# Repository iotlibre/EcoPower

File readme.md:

# EcoPower

Ecopower está pensado para tomar las medidas de consumo eléctrico de una vivienda o de un edificio con consumos inferiores a 30 KW. El sistema permite diferenciar varias zonas.

EcoPower se puede instalar en el cuadro eléctrico principal o en cualquier otra parte que nos permita tomar datos del consumo mediante pinzas (transformadores de intensidad).

En el un edificio podemos tener tantos dispositivos como sean necesarios y el servidor los integrará en la misma instalación sin necesidad de configuraciones adicionales o cambios en el Firmware.

La comunicación se hace mediante Wifi por lo que no es necesario el cableado de datos al equipo solamente es preciso que esté dentro de la cobertura de la red WIFI del edificio.

Para su uso no son necesarios conocimientos de informática aunque todos los desarrollos y el hardware están hechos bajo licencias libres lo que permite la modificación y mejora de las funcionalidades.

## Listado con las principales características
Las principales características de EcoPower son:
- 6 entradas para sensores de corriente con salida estandar de 50 mA
- 1 entrada de medida de voltage 200 - 440 Voltios
- Precisión en las medida de energía: ± 1,2%
- Comunicación a Internet por WIFI local 
- Configurable vía Web
- Estandard: IEEE 802.11 b/g/n
- Alimentación a 220 voltios de corriente alterna. Rango: 85 ~ 264VAC 
- Montaje en carril din
- La PCB integra un Arduino nano con el ESP8266 12E
- Compatible con el [servidor de Open Energy Monitor](https://emoncms.org/)

## Puesta a punto
La puesta a punto de EcoPower consta de dos partes:
- La configuración en la instalación
- El firmware de Arduino

### La configuración en la instalación
En este punto se definen los parámetros del servidor de destino y la wifi local a la que va a estar conectado el dispositivo. Con este fin, la primera vez que se ponga en servicio el ESP y siempre que no encuentre la WIFI configurada, el ESP 8266 12E creará su propio punto de acceso, su propia red WIFI . Conectandose a cualquier dirección a través de este punto de acceso nos aparecerá la página de configuración del ESP. Tengase en cuenta que una  vez configurado el ESP y conectado a una red WIFI el router le asignará una única dirección IP a la que será necesario acceder para cambiar la configuración.

En caso de que se quiera actualizar el firmware del ESP a la última versión, este se puede encontrar en: [EcoPower-emonESP ](https://github.com/iotlibre/20180328_EmonESP)

### El firmware de Arduino
El firmware que que esta cargado por defecto en el arduino nano funciona correctamente para tranformadores de intensidad de 100A/50mA sin embargo, si quiere cambiar la configuración puede encontrar la última actualización del firmware en este repositorio:[EcoPower-iotpow_serial ](https://github.com/iotlibre/EcoPower/tree/master/firmware/iotpower_serial/iotpow_serial)

## Source code
Copyright 2020 Endef Engineering SL.

Tanto el hardware como el software de este repositorio han sido desarrollados por la empresa: [Endef Engineering Sl](https://endef.com)

## Licencia
* Los diseños de hardware estan disponibles bajo licencia "Creative Commons Attribution-ShareAlike 3.0 Unported License.".
* El firmware se publica bajo la licencia GNU GPL V3 La documentación está sujeta a la Licencia "GNU Free Documentation"
* Los diseños de hardware siguen los términos de la Declaración de principios 1.0 de OSHW (Open-source hardware).

## Disclaimer
Todo el código que se encuentra en este repositorio está bajo la licencia: "GNU V3 General Public License" por lo que las condiciones de su uso son las incluidas en esta licencia

NUESTROS PRODUCTOS Y JUEGOS DE MONTAJE PUEDEN SER UTILIZADOS POR USUARIOS EXPERIMENTADOS Y CAPACITADOS BAJO SU PROPIO RIESGO. EN LA MEDIDA MÁXIMA QUE LO PERMITA LA LEY APLICABLE, POR EL PRESENTE RENUNCIAMOS CUALQUIER RESPONSABILIDAD, RIESGO Y DAÑOS DERIVADOS DE LA MUERTE O LESIONES PERSONALES RESULTANTES DEL MONTAJE O FUNCIONAMIENTO DE NUESTROS PRODUCTOS.

Su seguridad es su propia responsabilidad, incluido el uso adecuado del equipo y el equipo de seguridad, y determinar si tiene la habilidad y la experiencia adecuadas. Endef Engineering se exime de toda responsabilidad por cualquier daño, lesión o gasto resultante. Es su responsabilidad asegurarse de que sus actividades cumplan con las leyes aplicables, incluidos los derechos de autor. Puede haber actualizaciones o correcciones importantes. Todo uso de las instrucciones, kits, proyectos y sugerencias dadas por Endef Ingeniería es bajo su propio riesgo. La tecnología (hardware, firmware y software) cambia constantemente, es posible que la documentación (incluidas las instrucciones y la guía de compilación) no esté completa o sea correcta.

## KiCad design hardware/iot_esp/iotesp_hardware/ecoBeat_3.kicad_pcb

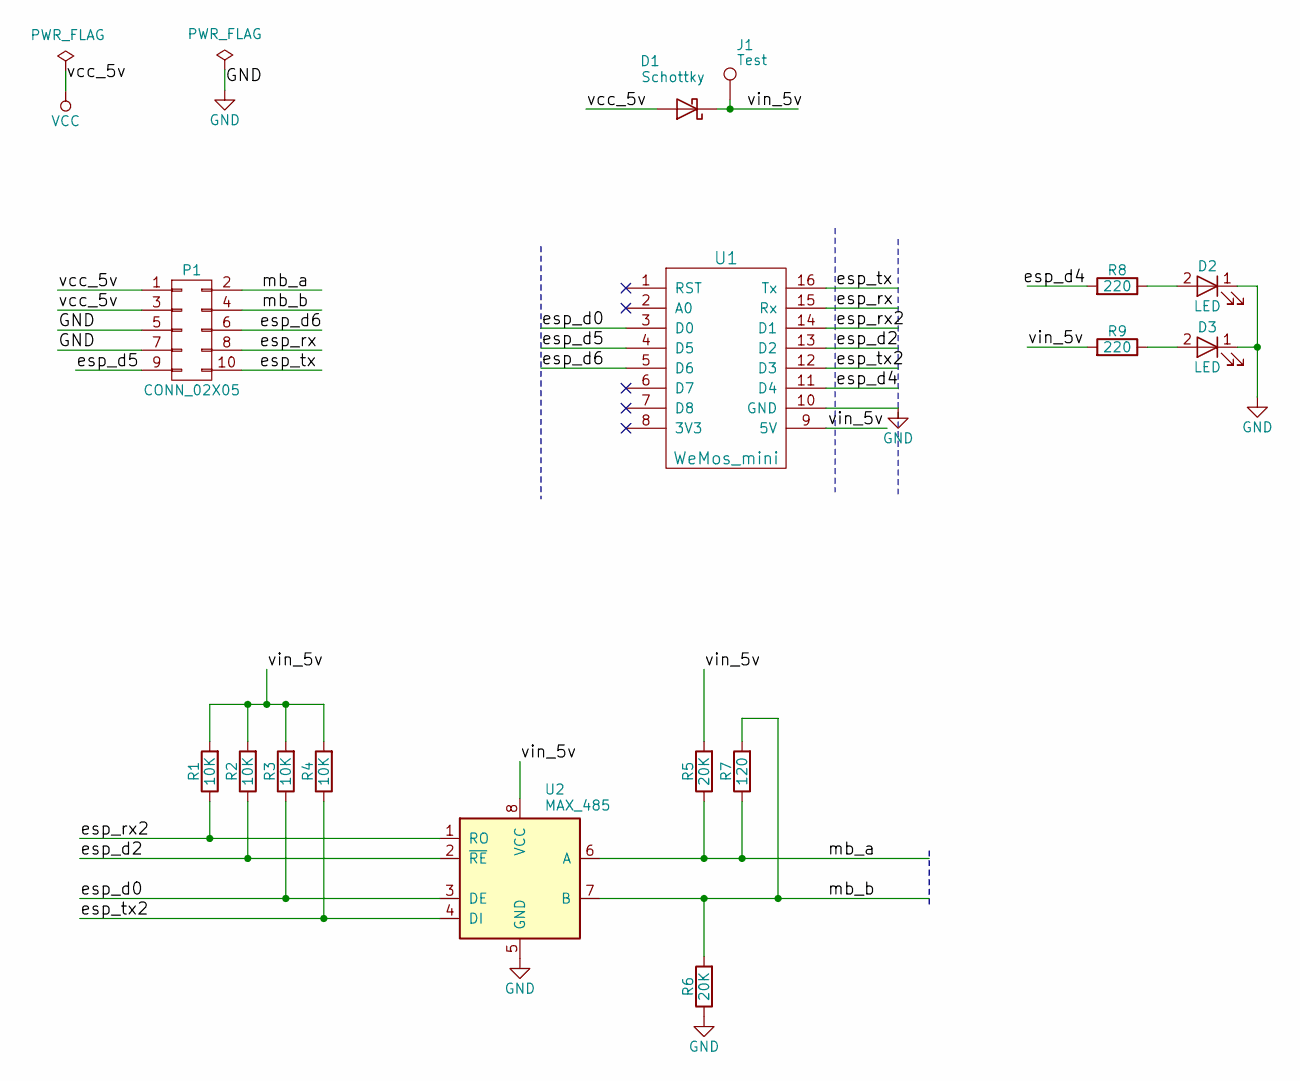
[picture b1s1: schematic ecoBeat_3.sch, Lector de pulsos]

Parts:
D1: Schottky; D_2114
D2, D3: LED; LED_D3.0mm
J1: Test; SolderWirePad_single_0-8mmDrill
P1: CONN_02X05; D1_mini_board
R1, R2, R3, R4: 10K; R_1206_HandSoldering
R5, R6: 20K; R_1206_HandSoldering
R7: 120; R_1206_HandSoldering
R8, R9: 220; R_1206_HandSoldering
U1: WeMos_mini; D1_mini_board_oscar
U2: MAX_485; SOIC-8-N

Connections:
/esp_d0: R3.1, U1.3 (D0), U2.3 (DE)
/esp_d2: R2.1, U1.13 (D2), U2.2 (~RE~)
/esp_d4: R8.2, U1.11 (D4)
/esp_d5: P1.9, U1.4 (D5)
/esp_d6: P1.6, U1.5 (D6)
/esp_rx: P1.8, U1.15 (Rx)
/esp_rx2: R1.1, U1.14 (D1), U2.1 (RO)
/esp_tx: P1.10, U1.16 (Tx)
/esp_tx2: R4.1, U1.12 (D3), U2.4 (DI)
/mb_a: P1.2, R5.1, R7.1, U2.6 (A)
/mb_b: P1.4, R6.2, R7.2, U2.7 (B)
/vin_5v: D1.1 (K), J1.1, R1.2, R2.2, R3.2, R4.2, R5.2, R9.2, U1.9 (5V), U2.8 (VCC)
GND: D2.1 (K), D3.1 (K), P1.5, P1.7, R6.1, U1.10 (GND), U2.5 (GND)
unnamed: D2.2 (A), R8.1
unnamed: D3.2 (A), R9.1
VCC: D1.2 (A), P1.1, P1.3

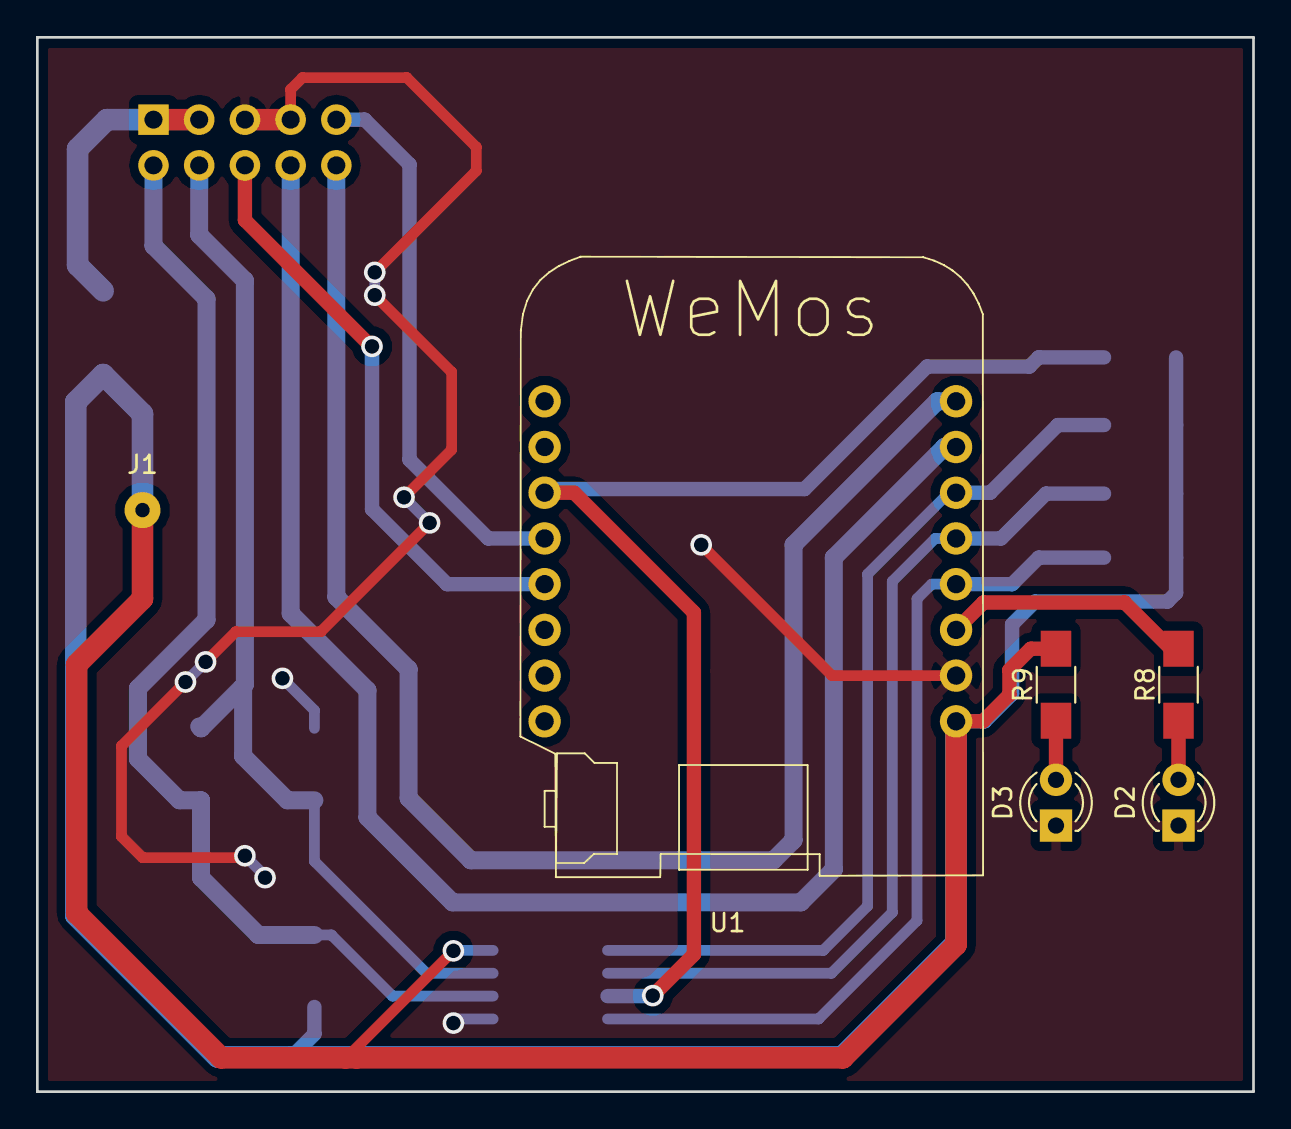
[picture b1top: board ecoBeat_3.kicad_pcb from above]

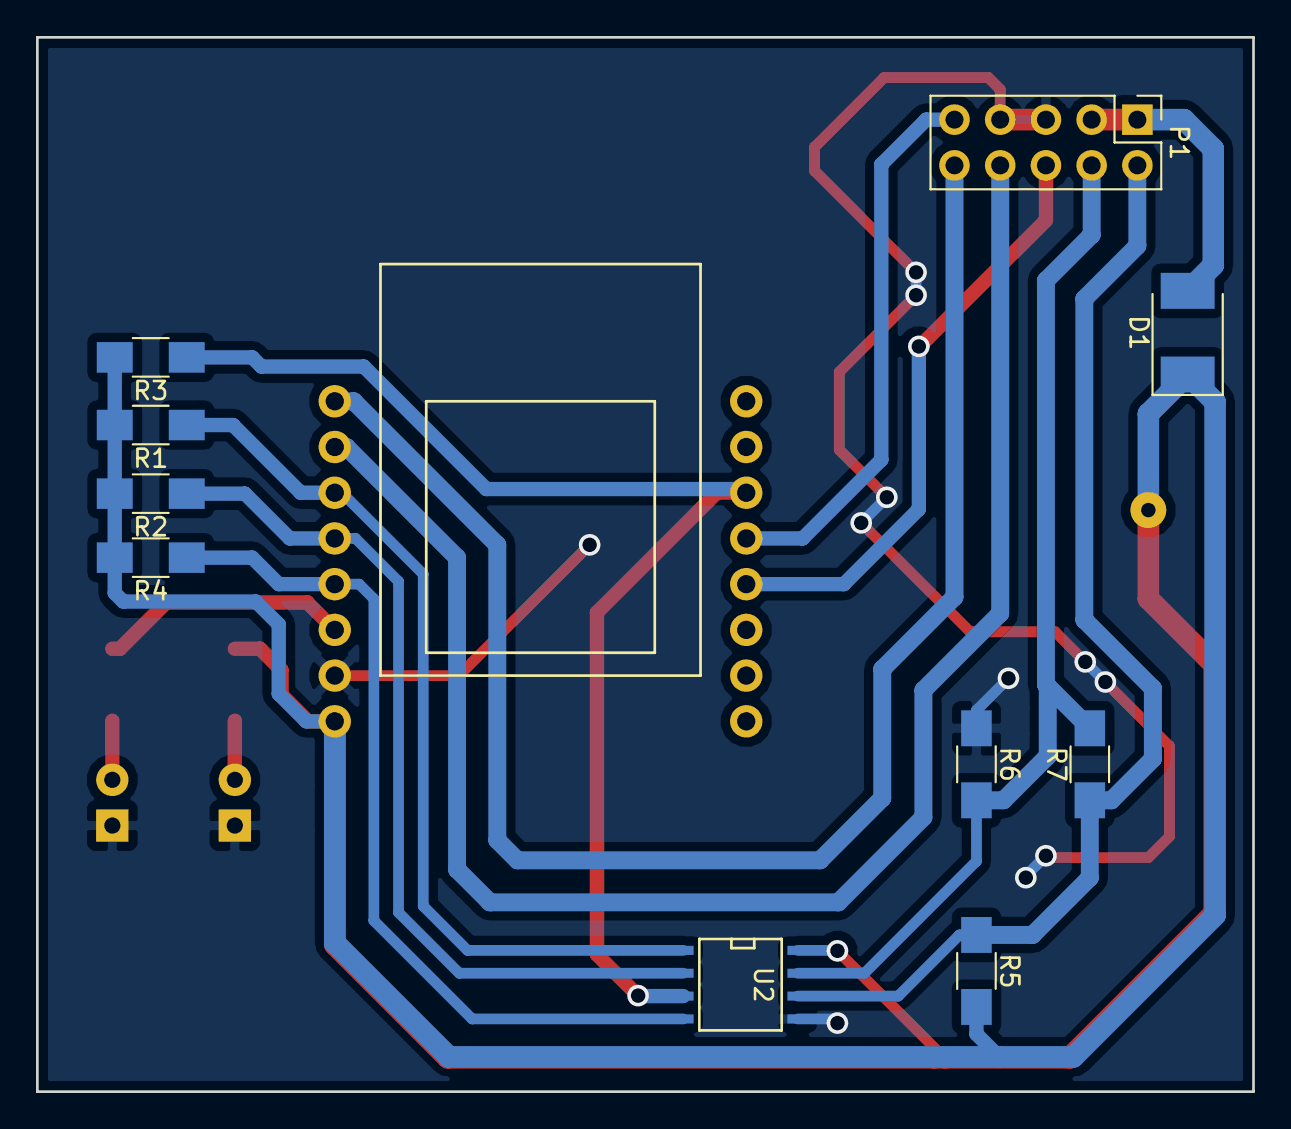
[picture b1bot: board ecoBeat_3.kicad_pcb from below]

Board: 2 copper layers, 67.6 x 58.6 mm, 16 parts (10 on the bottom side), 16 nets.

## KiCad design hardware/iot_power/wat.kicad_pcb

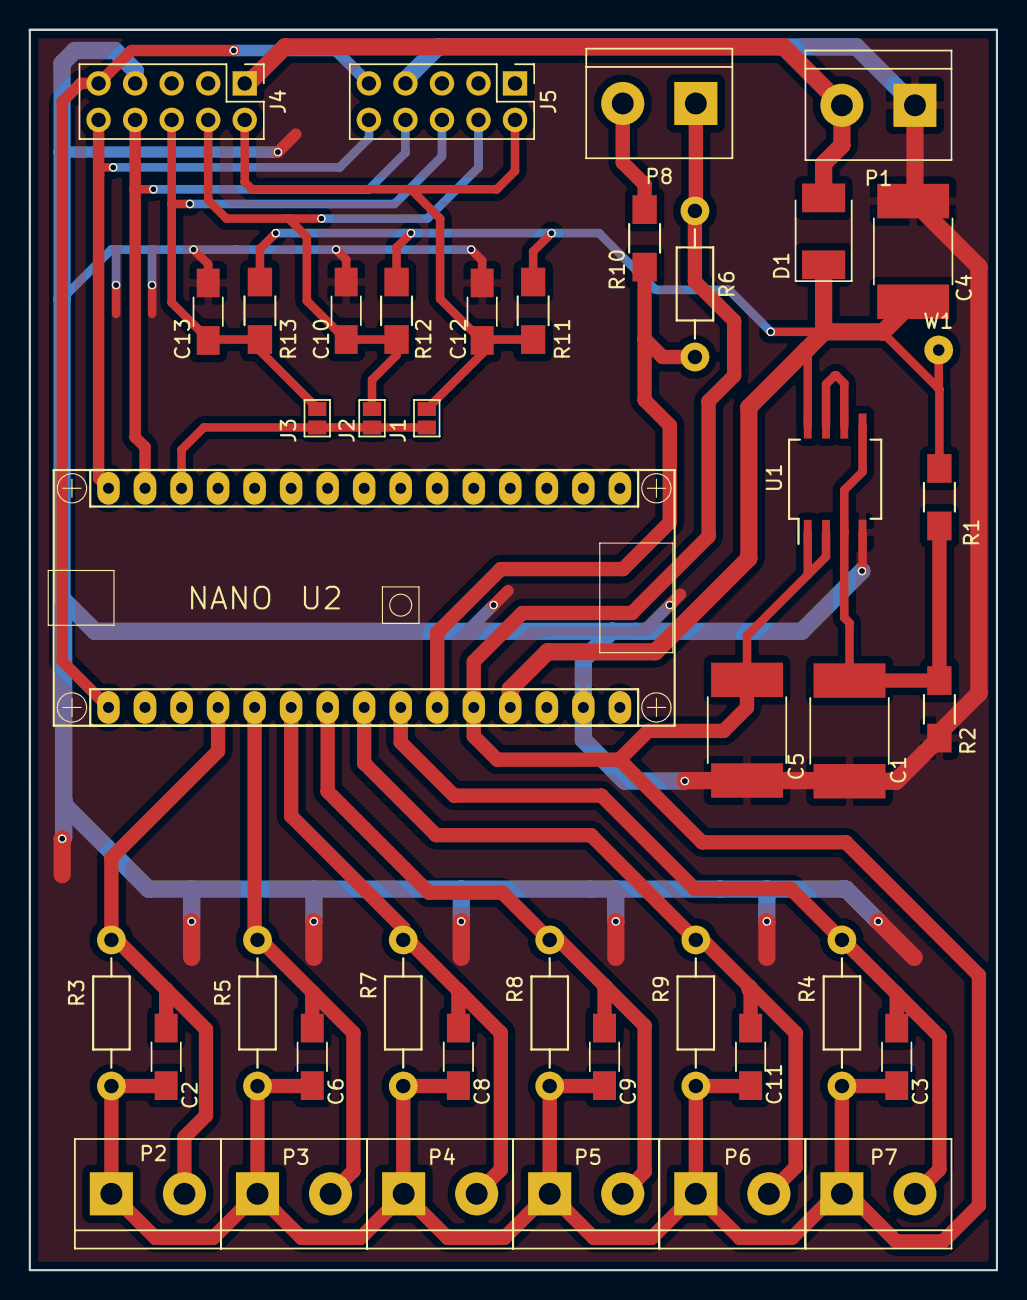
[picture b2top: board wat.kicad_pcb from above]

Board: 2 copper layers, 67.2 x 86.2 mm, 42 parts (0 on the bottom side), 21 nets.

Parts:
C1, C4, C5: 10uF; C_2220_HandSoldering
C2, C3, C6, C8, C9, C10, C11, C12, C13: 100nF; C_1206_HandSoldering
D1: schottky; D_2114
J1, J2, J3: GS2
J4, J5: Conn_02x05_Odd_Even; Pin_Header_Straight_2x05_Pitch2.54mm_onsar
P1: V_IN; TerminalBlock_bornier-2_P5.08mm
P2: PINZA_1; TerminalBlock_bornier-2_P5.08mm
P3: PINZA_2; TerminalBlock_bornier-2_P5.08mm
P4: PINZA_3; TerminalBlock_bornier-2_P5.08mm
P5: PINZA_4; TerminalBlock_bornier-2_P5.08mm
P6: PINZA_5; TerminalBlock_bornier-2_P5.08mm
P7: PINZA_6; TerminalBlock_bornier-2_P5.08mm
P8: PINZA_7; TerminalBlock_bornier-2_P5.08mm
R1, R2, R11, R12, R13: 4K7; R_1206_HandSoldering
R3, R4, R5, R7, R8, R9: 10k; Resistor_Horizontal_RM10mm
R6: 1k; Resistor_Horizontal_RM10mm
R10: 10k; R_1206_HandSoldering
U1: LM358; SO-8_5.3x6.2mm_Pitch1.27mm
U2: NANO; arduino_nano
W1: +5V; SolderWirePad_single_0-8mmDrill

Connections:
/esp_d0: C13.1, J3.2, J4.6, J5.6, R13.2
/esp_d1: C10.1, J2.2, J4.4, J5.4, R12.2
/esp_d2: C12.1, J1.2, J4.2, J5.2, R11.2
/intensidad_1: C2.1, P2.2, R3.1, U2.19
/intensidad_2: C6.1, P3.2, R5.1, U2.20
/intensidad_3: C8.1, P4.2, R7.1, U2.21
/intensidad_4: C9.1, P5.2, R8.1, U2.22
/intensidad_5: C11.1, P6.2, R9.1, U2.23
/intensidad_6: C3.1, P7.2, R4.1, U2.24
/miso: J4.10, J5.10, U2.15
/mosi: J4.8, J5.8, U2.14
/sck: J4.9, J5.9, U2.16
/ss: J1.1, J2.1, J3.1, U2.13
/v_25: C1.1, R1.2, R2.1, U1.3, U1.5
/v_referencia: C2.2, C3.2, C5.1, C6.2, C8.2, C9.2, C11.2, P2.1, P3.1, P4.1, P5.1, P6.1, P7.1, P8.1, R3.2, R4.2, R5.2, R6.2, R7.2, R8.2, R9.2, U1.1, U1.2, U2.26
/vcc_5v: D1.2, J4.1, P1.2
/voltage_1: R6.1, R10.1, U2.25
GND: C1.2, C4.2, C5.2, C10.2, C12.2, C13.2, J4.7, J5.7, P1.1, R2.2, U1.4, U2.29
unnamed: P8.2, R10.2
unnamed: U1.6, U1.7
VCC: C4.1, D1.1, R1.1, R11.1, R12.1, R13.1, U1.8, U2.27, W1.1

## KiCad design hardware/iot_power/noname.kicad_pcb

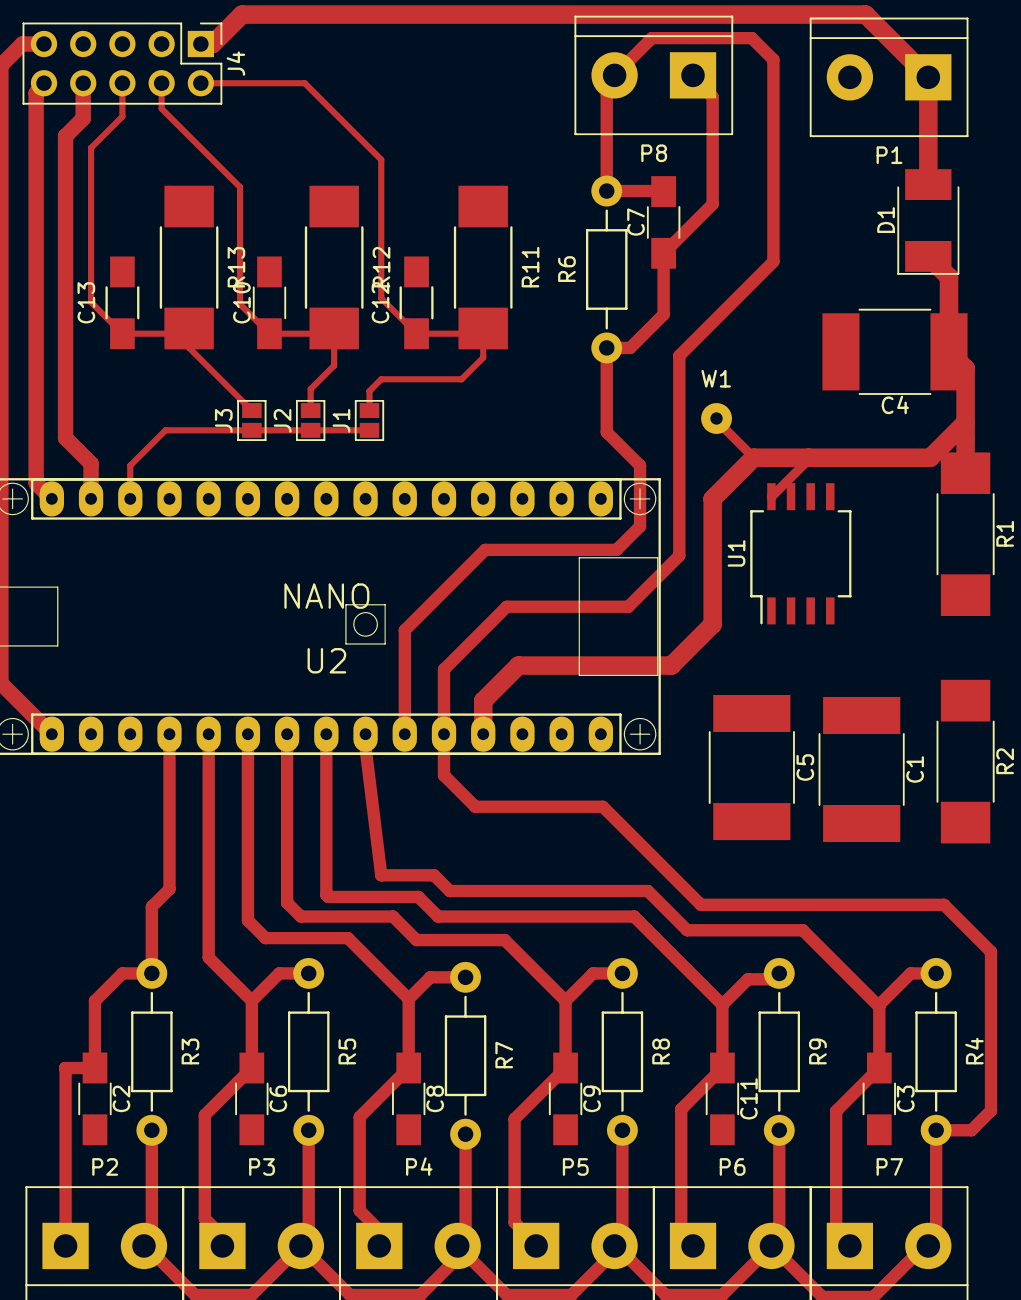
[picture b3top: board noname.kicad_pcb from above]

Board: 2 copper layers, 41 parts (0 on the bottom side), 19 nets.

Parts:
C1, C4, C5: 10uF; C_2220_HandSoldering
C2, C3, C6, C7, C8, C9, C10, C11, C12, C13: 100nF; C_1206_HandSoldering
D1: schottky; D_2114
J1, J2, J3: GS2
J4: Conn_02x05_Odd_Even; Pin_Header_Straight_2x05_Pitch2.54mm
P1: V_IN; TerminalBlock_bornier-2_P5.08mm
P2: PINZA_1; TerminalBlock_bornier-2_P5.08mm
P3: PINZA_2; TerminalBlock_bornier-2_P5.08mm
P4: PINZA_3; TerminalBlock_bornier-2_P5.08mm
P5: PINZA_4; TerminalBlock_bornier-2_P5.08mm
P6: PINZA_5; TerminalBlock_bornier-2_P5.08mm
P7: PINZA_6; TerminalBlock_bornier-2_P5.08mm
P8: PINZA_7; TerminalBlock_bornier-2_P5.08mm
R1, R2, R11, R12, R13: 4K7; R_2512_HandSoldering
R3, R4, R5, R6, R7, R8, R9: 10k; Resistor_Horizontal_RM10mm
U1: LM358; SO-8_5.3x6.2mm_Pitch1.27mm
U2: NANO; arduino_nano
W1: +5V; SolderWirePad_single_0-8mmDrill

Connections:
/esp_d0: C13.1, J3.2, J4.6, R13.2
/esp_d1: C10.1, J2.2, J4.4, R12.2
/esp_d2: C12.1, J1.2, J4.2, R11.2
/intensidad_1: C2.1, P2.1, R3.1, U2.19
/intensidad_2: C6.1, P3.1, R5.1, U2.20
/intensidad_3: C8.1, P4.1, R7.1, U2.21
/intensidad_4: C9.1, P5.1, R8.1, U2.22
/intensidad_5: C11.1, P6.1, R9.1, U2.23
/intensidad_6: C3.1, P7.1, R4.1, U2.24
/intensidad_7: C7.1, P8.1, R6.1, U2.25
/miso: J4.10, U2.15
/mosi: J4.8, U2.14
/sck: J4.9, U2.16
/ss: J1.1, J2.1, J3.1, U2.13
/v_referencia: C2.2, C3.2, C5.1, C6.2, C7.2, C8.2, C9.2, C11.2, P2.2, P3.2, P4.2, P5.2, P6.2, P7.2, P8.2, R3.2, R4.2, R5.2, R6.2, R7.2, R8.2, R9.2, U1.1, U1.2, U2.26
/vcc_5v: D1.2, J4.1, P1.1
GND: C1.2, C4.2, C5.2, C10.2, C12.2, C13.2, J4.7, P1.2, R2.2, U1.4, U2.29
unnamed: C1.1, R1.2, R2.1, U1.3
VCC: C4.1, D1.1, R1.1, R11.1, R12.1, R13.1, U1.8, U2.27, W1.1

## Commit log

2020-02-16 primera versión de produccion
2020-02-16 primera version readme
2020-02-16 edicion de readme
2020-02-16 edicion readme
2020-02-16 Parámetros principales de EcoPower
2020-02-20 facto de tension para transformadors Vac, factor de corriente para transformadores 400 0.1
2020-02-23 priemera varsion para medir tiempos de rele
2020-02-23 iotpower_onoff. version de producción
2020-03-02 constante transformador 8V
2022-05-26 Create LICENSE
